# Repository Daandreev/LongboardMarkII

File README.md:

# LongboardMarkII

Ground up, over-engineered electric longboard

*****August 8, 2017*****

I want something under my ass that has enough potential energy packed into its batteries to fire a pound of bacon into the Asteroid Belt. 
Since nothing on the market fits the bill; I am building it myself.

With a sufficient disrespect for my own time and money I am learning every EE, ME, CS, Manufacturing technique necessary to complete aforementioned longboard.

The project started in my freshman year of college, Winter 2015.

[MarkI](https://www.instructables.com/id/Electric-Longboard-Mark-I/) was completed in the spring of 2016. It featured a whopping 35mph top speed, a pair of lead-acid scooter batteries giving it a theoretical range of about 4 miles of range, and a jaguaresque construction - requiring field-repairs every 2 miles.

MarkII was started soon after. Initially I focused on learning the electrical engineering skills necessary to create the Motor Drivers, BMS, and Headlights. 
	The Motor Drivers were my introduction to H-bridges and after creating a design that could vaguely spin a BLDC motor I opted out for [Vedder's VESC](http://vedder.se/2015/01/vesc-open-source-esc/)
	The BMS vas envisioned as an adaptive system that could be daisy chained across as many batteries as necessary, however that became more of a PCB design and manufacturing learning experience after I learned more about how they are made industrially.
	The headlights were and still are massively successful. With 5 watts of pure photon emission created by a triple bank of German OSRAM diodes, they are blindingly bright in all Red, Green, Blue and White colors. The issue is that I cant run them on more than 10% brightness without facing serious heat management issues.
	
In parallel with the electronics, I created a few iterations of the deck. I constructed my own longboard-deck press by molding an initial foam model with cement. The initial few attempts at carbon fiber-foam composites failed, however on the 3rd iteration of the Baltic Birch - Carbon fiber Composite, I was able to produce a beautiful deck that stands at 48in tall and flexes less than an inch with 500lb on it.

I also learned how to use a few CAD packages, and CNC equipment to make the mounting hardware for the motors. Learning from the flimsy construction of the MarkI motor mounts I designed my own longboard trucks to accommodate the installation of a pair of 2250Watt motors. My designs were based on the Caliber II Longboard trucks.

As it stands, just about everything made in the past year needs to be reiterated.

My main focus now, is to involve more people. My friend Anton Zaytsev has been diligently helping me create a 1.5kW charger and another offered to do some of the software. However, I think this project can bring together a serious community interested in progressing high-tech DIY electrical vehicles.

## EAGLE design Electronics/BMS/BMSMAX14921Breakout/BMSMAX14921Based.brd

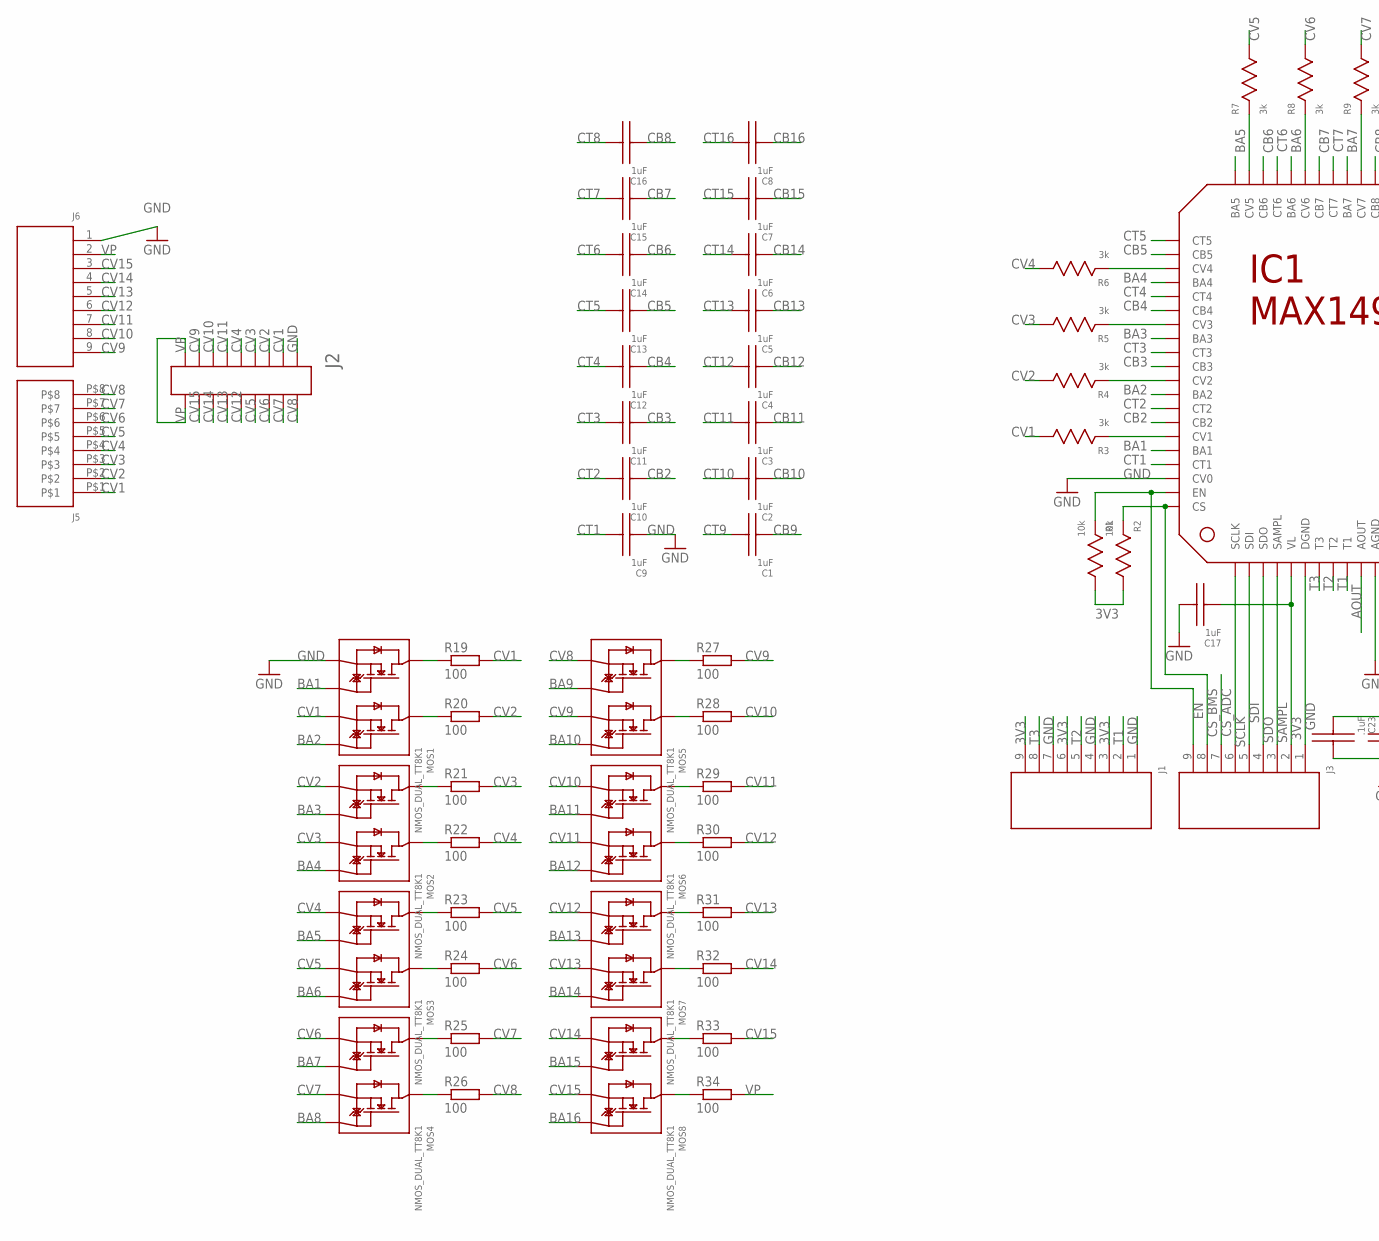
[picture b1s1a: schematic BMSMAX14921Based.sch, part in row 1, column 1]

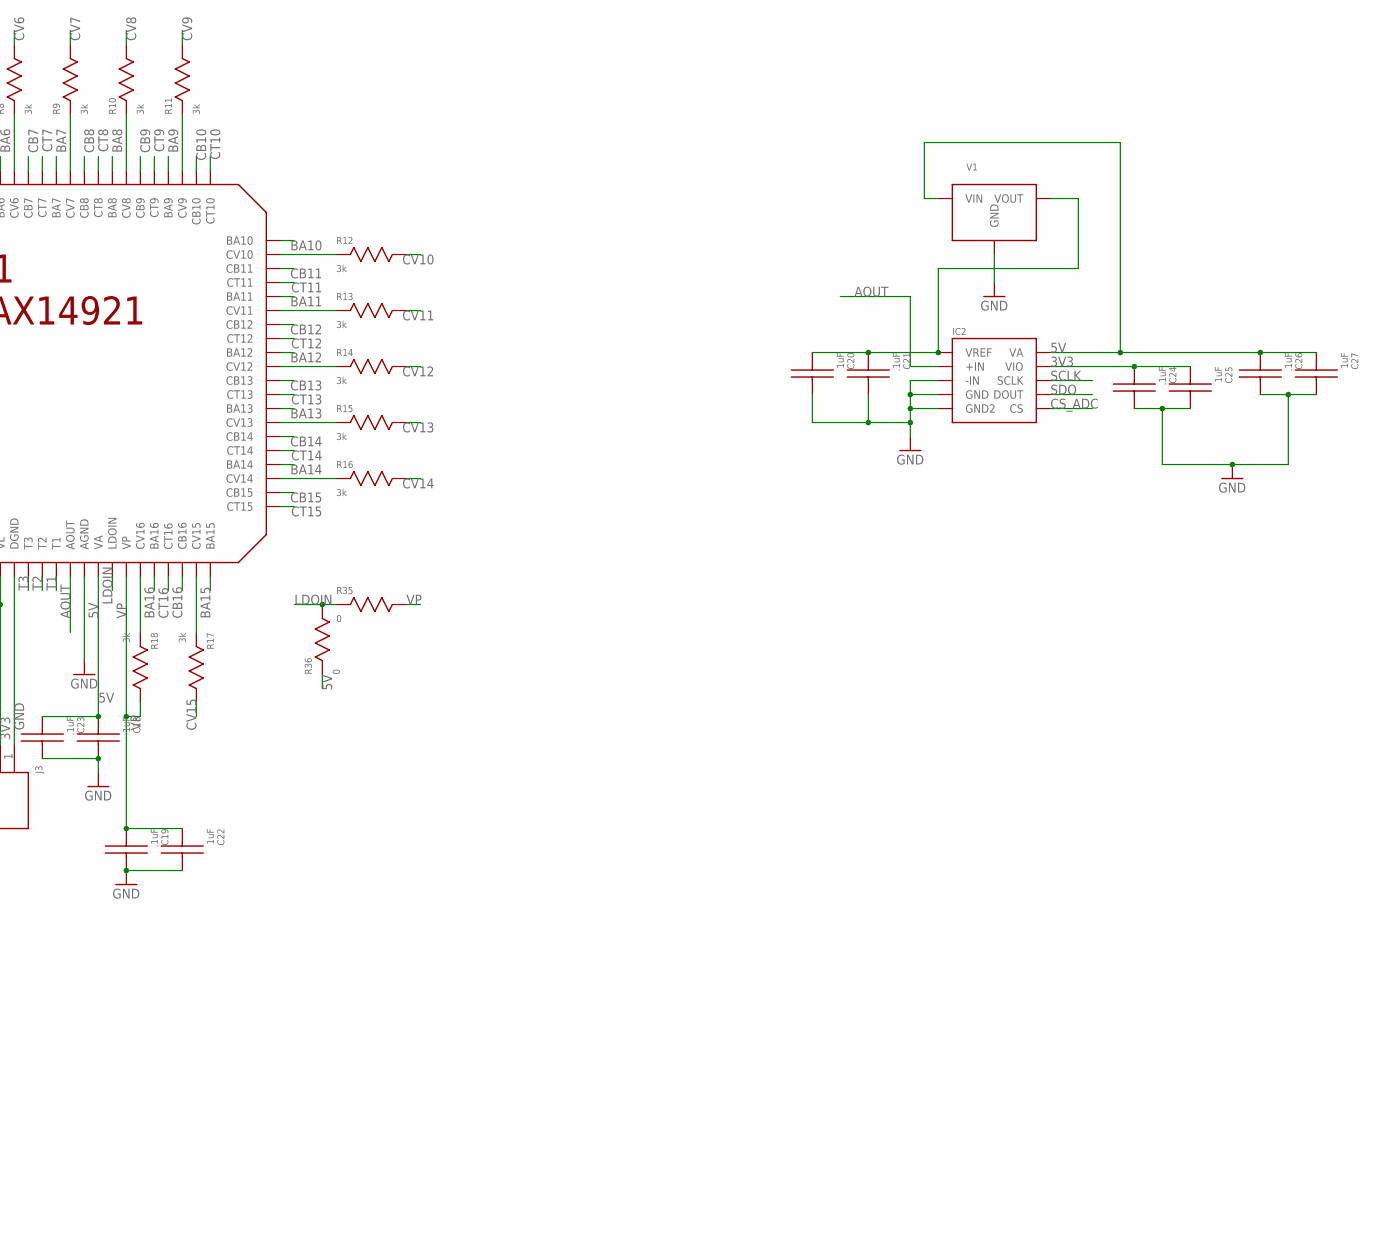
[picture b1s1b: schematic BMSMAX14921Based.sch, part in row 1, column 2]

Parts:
C1, C2, C3, C4, C5, C6, C7, C8, C9, C10, C11, C12, C13, C14, C15, C16, C17, C18, C20, C22, C25, C27: 1uF; 0805_(2012_METRIC)
C19, C21, C23, C24, C26: .1uF; 0805_(2012_METRIC)
IC1: MAX14921; 80TQFP
IC2: ADC141S626; 10-VSSOP
J1, J3, J6: CONNECTOR_9PIN; 9PIN_.1'
J2: CONNECTORJST2X9_2MM; CONNECTOR9X2_2MMPITCH
J5: CONNECTOR_8PIN; 8PIN_.1'
MOS1, MOS2, MOS3, MOS4, MOS5, MOS6, MOS7, MOS8: NMOS_DUAL_TT8K1; TSST8
R1, R2: 10k; 0805_(2012_METRIC)
R3, R4, R5, R6, R7, R8, R9, R10, R11, R12, R13, R14, R15, R16, R17, R18: 3k; 0805_(2012_METRIC)
R19, R20, R21, R22, R23, R24, R25, R26, R27, R28, R29, R30, R31, R32, R33, R34: 100; 0411V
R35, R36: 0; 0805_(2012_METRIC)
V1: REF3040; SOT-23

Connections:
3V3: C17.P$2, C24.P$2, C25.P$2, IC1.P$5 (VL), IC2.P$9 (VIO), J1.3, J1.6, J1.9, J3.2, R1.P$1, R2.P$1
5V: C18.P$2, C23.P$2, C26.P$2, C27.P$2, IC1.P$12 (VA), IC2.P$10 (VA), R36.P$2, V1.1 (VIN)
AOUT: IC1.P$10 (AOUT), IC2.P$2 (+IN)
BA1: IC1.P$76 (BA1), MOS1.P$2 (G1)
BA2: IC1.P$72 (BA2), MOS1.P$4 (G2)
BA3: IC1.P$68 (BA3), MOS2.P$2 (G1)
BA4: IC1.P$64 (BA4), MOS2.P$4 (G2)
BA5: IC1.P$60 (BA5), MOS3.P$2 (G1)
BA6: IC1.P$56 (BA6), MOS3.P$4 (G2)
BA7: IC1.P$52 (BA7), MOS4.P$2 (G1)
BA8: IC1.P$48 (BA8), MOS4.P$4 (G2)
BA9: IC1.P$44 (BA9), MOS5.P$2 (G1)
BA10: IC1.P$40 (BA10), MOS5.P$4 (G2)
BA11: IC1.P$36 (BA11), MOS6.P$2 (G1)
BA12: IC1.P$32 (BA12), MOS6.P$4 (G2)
BA13: IC1.P$28 (BA13), MOS7.P$2 (G1)
BA14: IC1.P$24 (BA14), MOS7.P$4 (G2)
BA15: IC1.P$20 (BA15), MOS8.P$2 (G1)
BA16: IC1.P$16 (BA16), MOS8.P$4 (G2)
CB2: C10.P$2, IC1.P$74 (CB2)
CB3: C11.P$2, IC1.P$70 (CB3)
CB4: C12.P$2, IC1.P$66 (CB4)
CB5: C13.P$2, IC1.P$62 (CB5)
CB6: C14.P$2, IC1.P$58 (CB6)
CB7: C15.P$2, IC1.P$54 (CB7)
CB8: C16.P$2, IC1.P$50 (CB8)
CB9: C1.P$2, IC1.P$46 (CB9)
CB10: C2.P$2, IC1.P$42 (CB10)
CB11: C3.P$2, IC1.P$38 (CB11)
CB12: C4.P$2, IC1.P$34 (CB12)
CB13: C5.P$2, IC1.P$30 (CB13)
CB14: C6.P$2, IC1.P$26 (CB14)
CB15: C7.P$2, IC1.P$22 (CB15)
CB16: C8.P$2, IC1.P$18 (CB16)
CS_ADC: IC2.P$6 (CS), J3.7
CS_BMS: IC1.P$80 (CS), J3.8, R2.P$2
CT1: C9.P$1, IC1.P$77 (CT1)
CT2: C10.P$1, IC1.P$73 (CT2)
CT3: C11.P$1, IC1.P$69 (CT3)
CT4: C12.P$1, IC1.P$65 (CT4)
CT5: C13.P$1, IC1.P$61 (CT5)
CT6: C14.P$1, IC1.P$57 (CT6)
CT7: C15.P$1, IC1.P$53 (CT7)
CT8: C16.P$1, IC1.P$49 (CT8)
CT9: C1.P$1, IC1.P$45 (CT9)
CT10: C2.P$1, IC1.P$41 (CT10)
CT11: C3.P$1, IC1.P$37 (CT11)
CT12: C4.P$1, IC1.P$33 (CT12)
CT13: C5.P$1, IC1.P$29 (CT13)
CT14: C6.P$1, IC1.P$25 (CT14)
CT15: C7.P$1, IC1.P$21 (CT15)
CT16: C8.P$1, IC1.P$17 (CT16)
CV1: J2.P$2, J5.P$1, MOS1.P$3 (S2), R3.P$1, R19.2
CV2: J2.P$3, J5.P$2, MOS2.P$1 (S1), R4.P$1, R20.2
CV3: J2.P$4, J5.P$3, MOS2.P$3 (S2), R5.P$1, R21.2
CV4: J2.P$5, J5.P$4, MOS3.P$1 (S1), R6.P$1, R22.2
CV5: J2.P$15, J5.P$5, MOS3.P$3 (S2), R7.P$1, R23.2
CV6: J2.P$16, J5.P$6, MOS4.P$1 (S1), R8.P$1, R24.2
CV7: J2.P$17, J5.P$7, MOS4.P$3 (S2), R9.P$1, R25.2
CV8: J2.P$18, J5.P$8, MOS5.P$1 (S1), R10.P$1, R26.2
CV9: J2.P$8, J6.9, MOS5.P$3 (S2), R11.P$1, R27.2
CV10: J2.P$7, J6.8, MOS6.P$1 (S1), R12.P$1, R28.2
CV11: J2.P$6, J6.7, MOS6.P$3 (S2), R13.P$1, R29.2
CV12: J2.P$14, J6.6, MOS7.P$1 (S1), R14.P$1, R30.2
CV13: J2.P$13, J6.5, MOS7.P$3 (S2), R15.P$1, R31.2
CV14: J2.P$12, J6.4, MOS8.P$1 (S1), R16.P$1, R32.2
CV15: J2.P$11, J6.3, MOS8.P$3 (S2), R17.P$1, R33.2
EN: IC1.P$79 (EN), J3.9, R1.P$2
GND: C9.P$2, C17.P$1, C18.P$1, C19.P$1, C20.P$1, C21.P$1, C22.P$1, C23.P$1, C24.P$1, C25.P$1, C26.P$1, C27.P$1, IC1.P$6 (DGND), IC1.P$11 (AGND), IC1.P$78 (CV0), IC2.P$3 (-IN), IC2.P$4 (GND), IC2.P$5 (GND2), J1.1, J1.4, J1.7, J2.P$1, J3.1, J6.1, MOS1.P$1 (S1), V1.3 (GND)
LDOIN: IC1.P$13 (LDOIN), R35.P$2, R36.P$1
unnamed: MOS1.P$7 (D1), MOS1.P$8 (D1), R19.1
unnamed: C20.P$2, C21.P$2, IC2.P$1 (VREF), V1.2 (VOUT)
unnamed: IC1.P$71 (CV2), R4.P$2
unnamed: IC1.P$67 (CV3), R5.P$2
unnamed: IC1.P$75 (CV1), R3.P$2
unnamed: IC1.P$63 (CV4), R6.P$2
unnamed: IC1.P$59 (CV5), R7.P$2
unnamed: IC1.P$55 (CV6), R8.P$2
unnamed: IC1.P$51 (CV7), R9.P$2
unnamed: IC1.P$47 (CV8), R10.P$2
unnamed: IC1.P$43 (CV9), R11.P$2
unnamed: IC1.P$39 (CV10), R12.P$2
unnamed: IC1.P$35 (CV11), R13.P$2
unnamed: IC1.P$31 (CV12), R14.P$2
unnamed: IC1.P$27 (CV13), R15.P$2
unnamed: IC1.P$23 (CV14), R16.P$2
unnamed: IC1.P$19 (CV15), R17.P$2
unnamed: IC1.P$15 (CV16), R18.P$2
unnamed: MOS1.P$5 (D2), MOS1.P$6 (D2), R20.1
unnamed: MOS2.P$7 (D1), MOS2.P$8 (D1), R21.1
unnamed: MOS2.P$5 (D2), MOS2.P$6 (D2), R22.1
unnamed: MOS3.P$7 (D1), MOS3.P$8 (D1), R23.1
unnamed: MOS3.P$5 (D2), MOS3.P$6 (D2), R24.1
unnamed: MOS4.P$7 (D1), MOS4.P$8 (D1), R25.1
unnamed: MOS4.P$5 (D2), MOS4.P$6 (D2), R26.1
unnamed: MOS5.P$7 (D1), MOS5.P$8 (D1), R27.1
unnamed: MOS5.P$5 (D2), MOS5.P$6 (D2), R28.1
unnamed: MOS6.P$7 (D1), MOS6.P$8 (D1), R29.1
unnamed: MOS6.P$5 (D2), MOS6.P$6 (D2), R30.1
unnamed: MOS7.P$7 (D1), MOS7.P$8 (D1), R31.1
unnamed: MOS7.P$5 (D2), MOS7.P$6 (D2), R32.1
unnamed: MOS8.P$7 (D1), MOS8.P$8 (D1), R33.1
unnamed: MOS8.P$5 (D2), MOS8.P$6 (D2), R34.1
SAMPL: IC1.P$4 (SAMPL), J3.3
SCLK: IC1.P$1 (SCLK), IC2.P$8 (SCLK), J3.6
SDI: IC1.P$2 (SDI), J3.5
SDO: IC1.P$3 (SDO), IC2.P$7 (DOUT), J3.4
T1: IC1.P$9 (T1), J1.2
T2: IC1.P$8 (T2), J1.5
T3: IC1.P$7 (T3), J1.8
VP: C19.P$2, C22.P$2, IC1.P$14 (VP), J2.P$9, J2.P$10, J6.2, R18.P$1, R34.2, R35.P$1

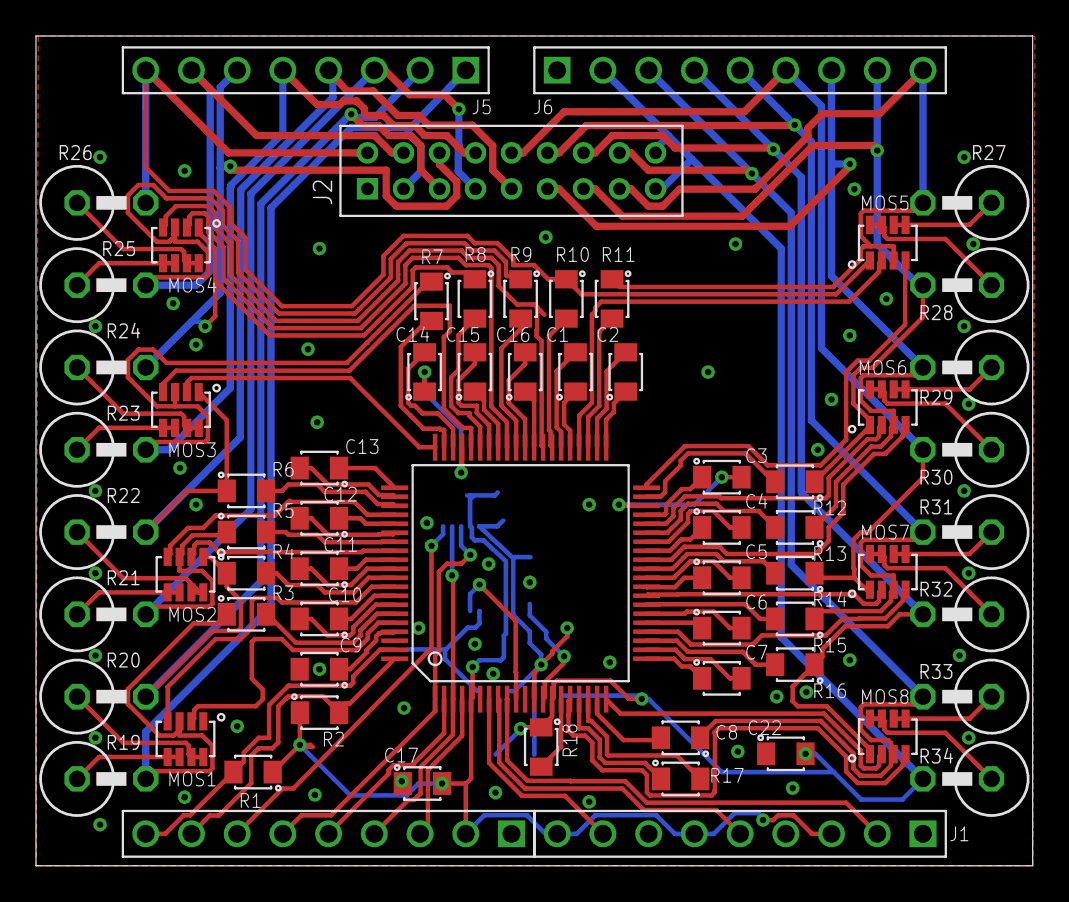
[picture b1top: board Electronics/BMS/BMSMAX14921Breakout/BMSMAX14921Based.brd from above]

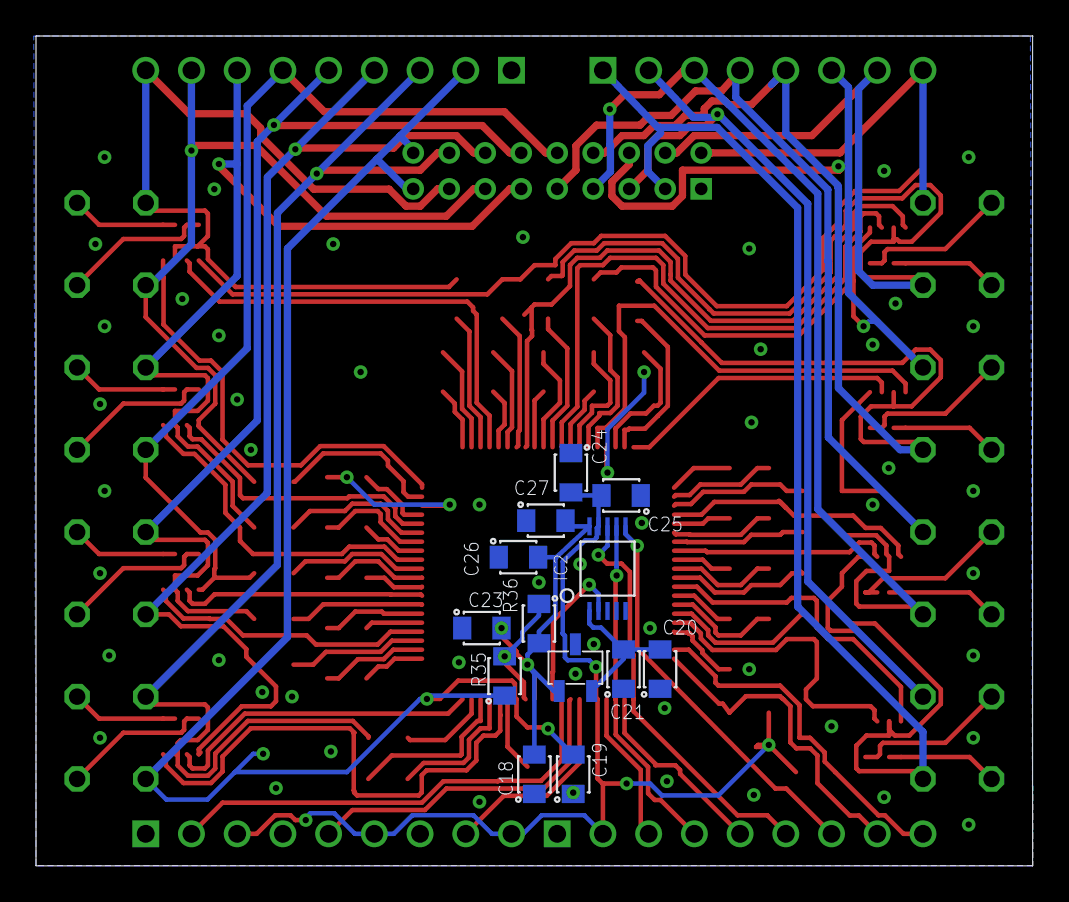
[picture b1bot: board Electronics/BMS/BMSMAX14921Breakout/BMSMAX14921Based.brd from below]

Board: 2 copper layers, 55.4 x 46.1 mm, 79 parts (13 on the bottom side), 111 nets.

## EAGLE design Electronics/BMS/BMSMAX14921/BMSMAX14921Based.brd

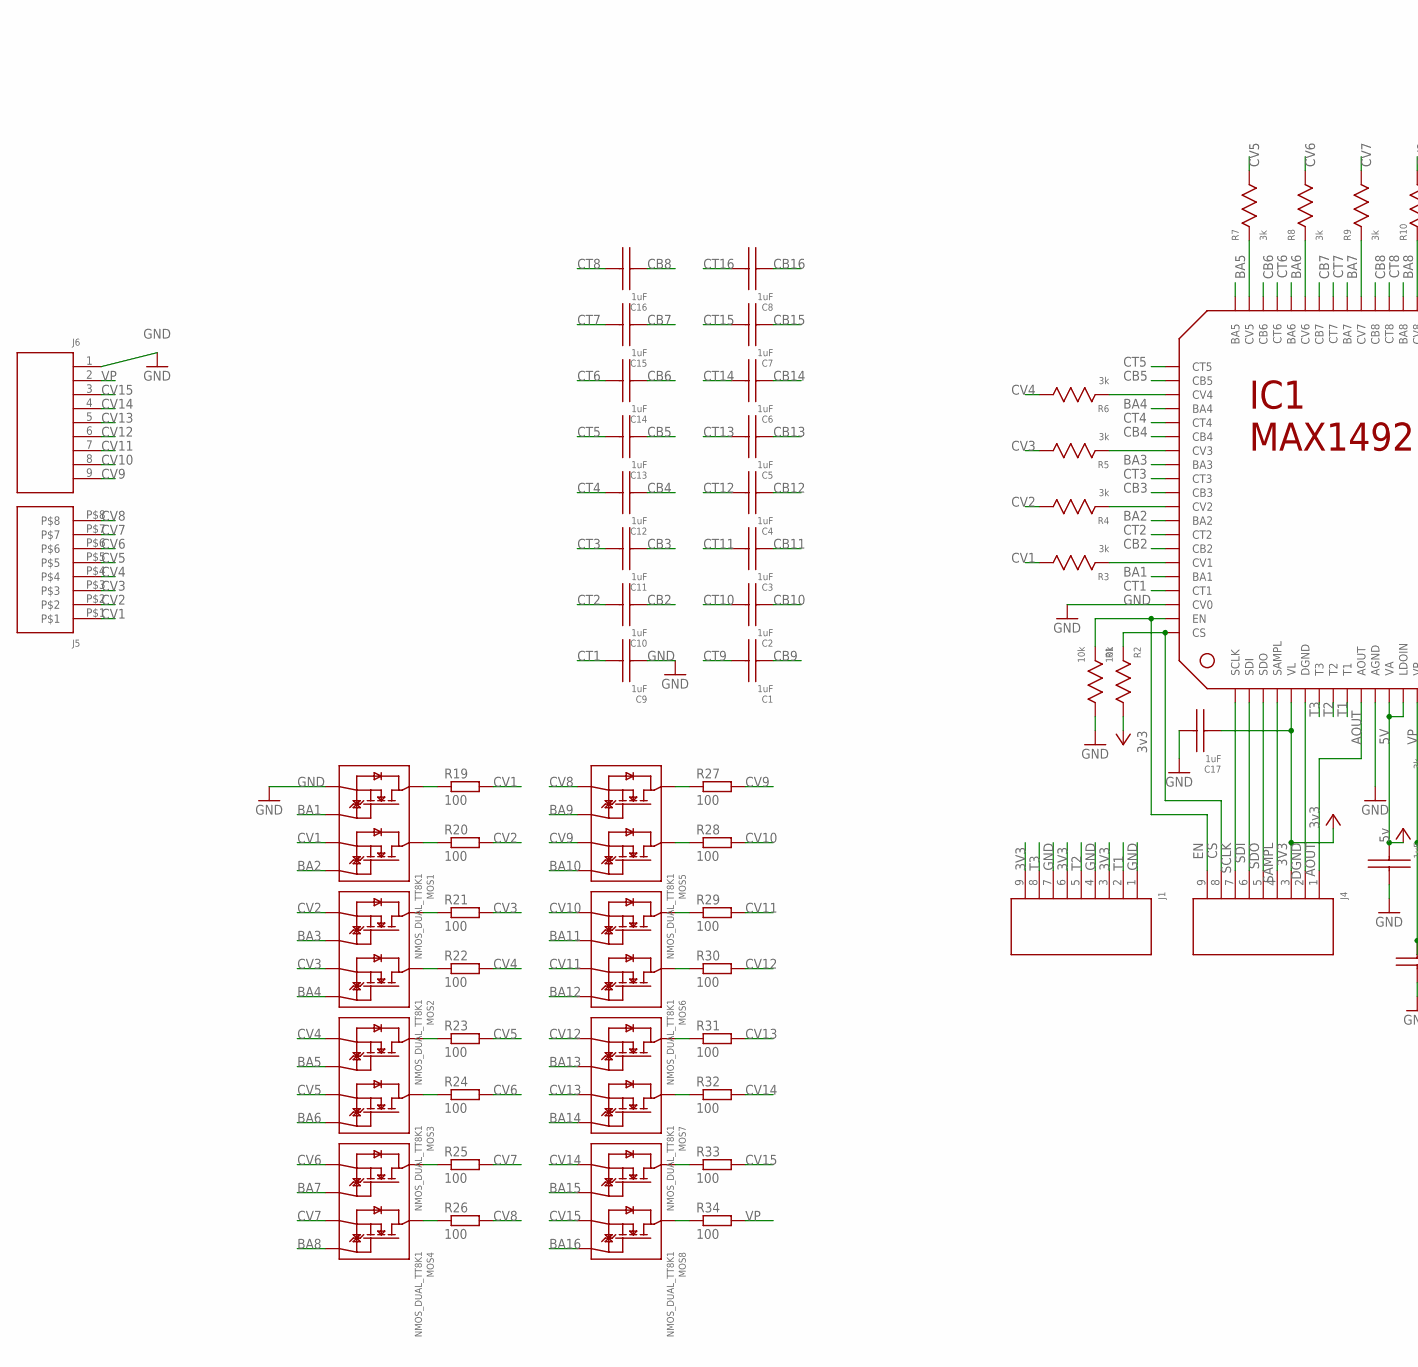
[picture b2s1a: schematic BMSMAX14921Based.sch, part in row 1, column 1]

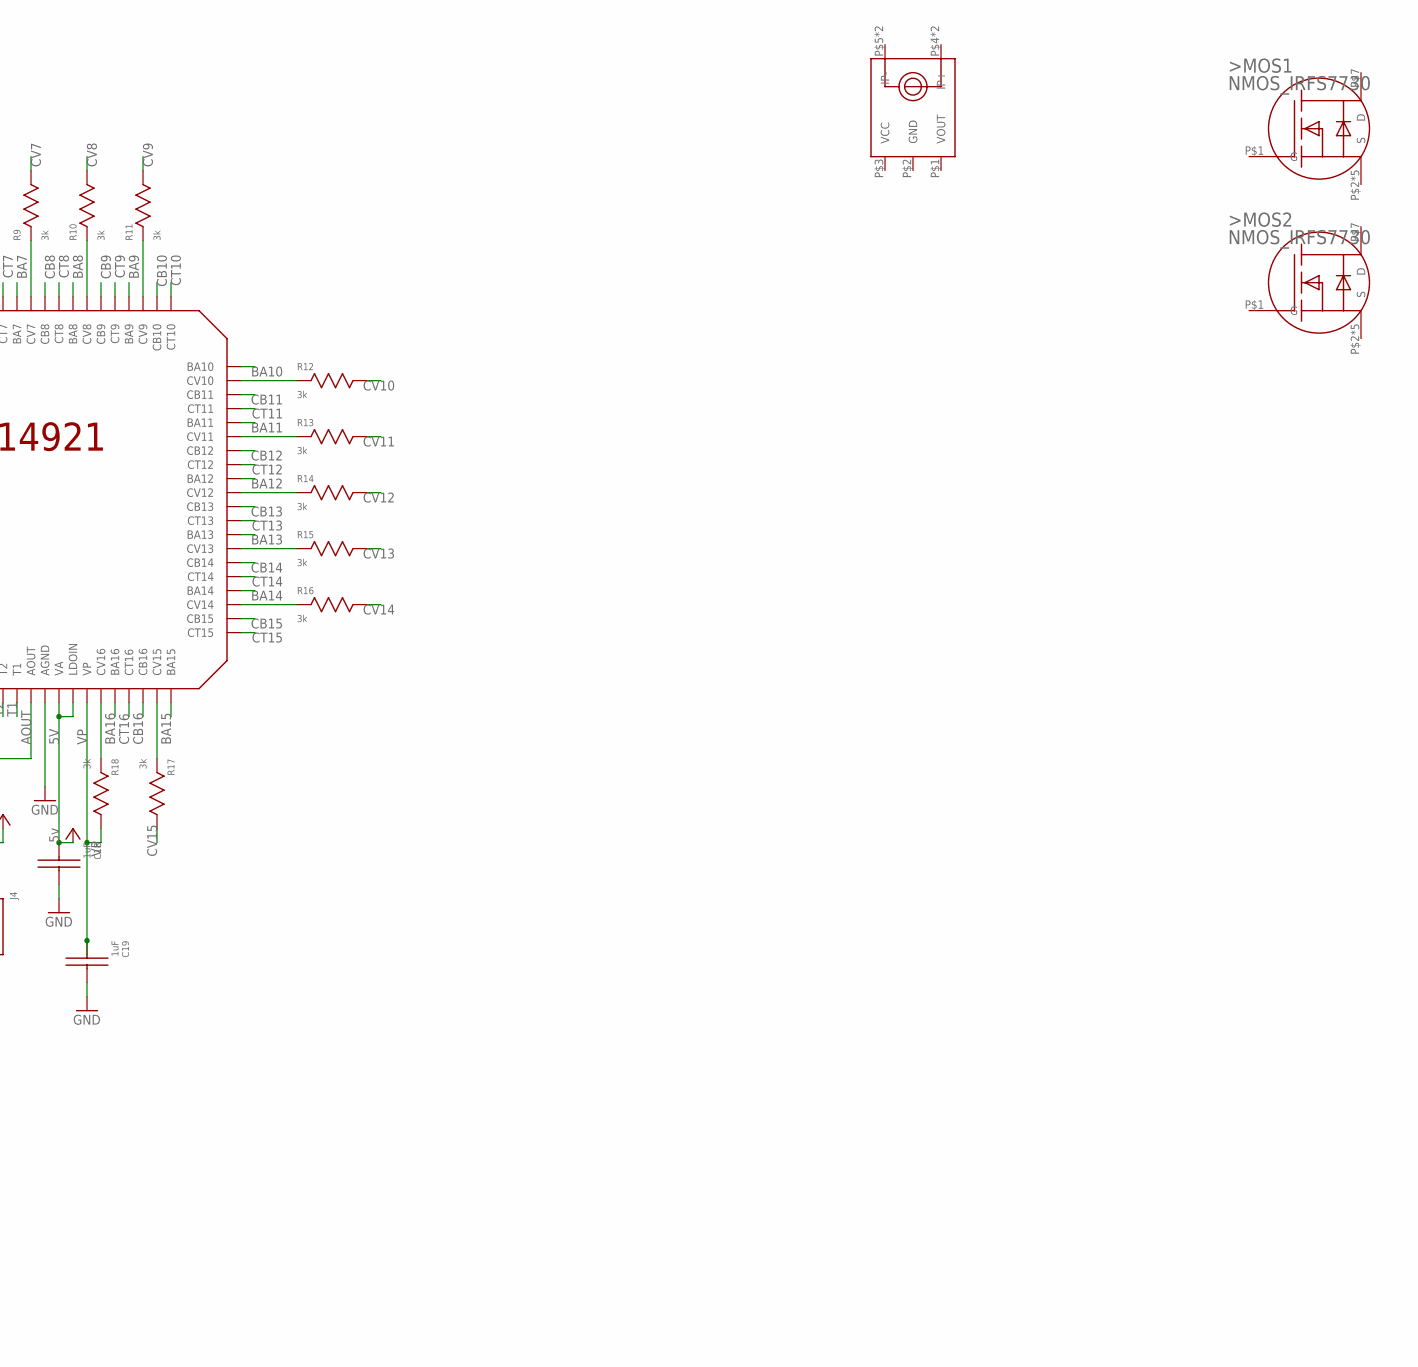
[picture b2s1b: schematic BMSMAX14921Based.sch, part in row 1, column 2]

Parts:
>MOS1, >MOS2: NMOS_IRFS7730; D2PAK-7PIN
C1, C2, C3, C4, C5, C6, C7, C8, C9, C10, C11, C12, C13, C14, C15, C16, C17, C18, C19: 1uF; 0805_(2012_METRIC)
IC1: MAX14921; 80TQFP
J1, J4, J6: CONNECTOR_9PIN; 9PIN_.1'
J5: CONNECTOR_8PIN; 8PIN_.1'
MOS1, MOS2, MOS3, MOS4, MOS5, MOS6, MOS7, MOS8: NMOS_DUAL_TT8K1; TSST8
R1, R2: 10k; 0805_(2012_METRIC)
R3, R4, R5, R6, R7, R8, R9, R10, R11, R12, R13, R14, R15, R16, R17, R18: 3k; 0805_(2012_METRIC)
R19, R20, R21, R22, R23, R24, R25, R26, R27, R28, R29, R30, R31, R32, R33, R34: 100; 0411V
U$1: ACS758XCB; CB5PFF

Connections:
3V3: C17.P$2, IC1.5 (VL), J1.3, J1.6, J1.9, J4.3, R2.P$1
5V: C18.P$2, IC1.12 (VA), IC1.13 (LDOIN)
AOUT: IC1.10 (AOUT), J4.1
BA1: IC1.76 (BA1), MOS1.P$2 (G1)
BA2: IC1.72 (BA2), MOS1.P$4 (G2)
BA3: IC1.68 (BA3), MOS2.P$2 (G1)
BA4: IC1.64 (BA4), MOS2.P$4 (G2)
BA5: IC1.60 (BA5), MOS3.P$2 (G1)
BA6: IC1.56 (BA6), MOS3.P$4 (G2)
BA7: IC1.52 (BA7), MOS4.P$2 (G1)
BA8: IC1.48 (BA8), MOS4.P$4 (G2)
BA9: IC1.44 (BA9), MOS5.P$2 (G1)
BA10: IC1.40 (BA10), MOS5.P$4 (G2)
BA11: IC1.36 (BA11), MOS6.P$2 (G1)
BA12: IC1.32 (BA12), MOS6.P$4 (G2)
BA13: IC1.28 (BA13), MOS7.P$2 (G1)
BA14: IC1.24 (BA14), MOS7.P$4 (G2)
BA15: IC1.20 (BA15), MOS8.P$2 (G1)
BA16: IC1.16 (BA16), MOS8.P$4 (G2)
CB2: C10.P$2, IC1.74 (CB2)
CB3: C11.P$2, IC1.70 (CB3)
CB4: C12.P$2, IC1.66 (CB4)
CB5: C13.P$2, IC1.62 (CB5)
CB6: C14.P$2, IC1.58 (CB6)
CB7: C15.P$2, IC1.54 (CB7)
CB8: C16.P$2, IC1.50 (CB8)
CB9: C1.P$2, IC1.46 (CB9)
CB10: C2.P$2, IC1.42 (CB10)
CB11: C3.P$2, IC1.38 (CB11)
CB12: C4.P$2, IC1.34 (CB12)
CB13: C5.P$2, IC1.30 (CB13)
CB14: C6.P$2, IC1.26 (CB14)
CB15: C7.P$2, IC1.22 (CB15)
CB16: C8.P$2, IC1.18 (CB16)
CS: IC1.80 (CS), J4.8, R2.P$2
CT1: C9.P$1, IC1.77 (CT1)
CT2: C10.P$1, IC1.73 (CT2)
CT3: C11.P$1, IC1.69 (CT3)
CT4: C12.P$1, IC1.65 (CT4)
CT5: C13.P$1, IC1.61 (CT5)
CT6: C14.P$1, IC1.57 (CT6)
CT7: C15.P$1, IC1.53 (CT7)
CT8: C16.P$1, IC1.49 (CT8)
CT9: C1.P$1, IC1.45 (CT9)
CT10: C2.P$1, IC1.41 (CT10)
CT11: C3.P$1, IC1.37 (CT11)
CT12: C4.P$1, IC1.33 (CT12)
CT13: C5.P$1, IC1.29 (CT13)
CT14: C6.P$1, IC1.25 (CT14)
CT15: C7.P$1, IC1.21 (CT15)
CT16: C8.P$1, IC1.17 (CT16)
CV1: J5.P$1, MOS1.P$3 (S2), R3.P$1, R19.2
CV2: J5.P$2, MOS2.P$1 (S1), R4.P$1, R20.2
CV3: J5.P$3, MOS2.P$3 (S2), R5.P$1, R21.2
CV4: J5.P$4, MOS3.P$1 (S1), R6.P$1, R22.2
CV5: J5.P$5, MOS3.P$3 (S2), R7.P$1, R23.2
CV6: J5.P$6, MOS4.P$1 (S1), R8.P$1, R24.2
CV7: J5.P$7, MOS4.P$3 (S2), R9.P$1, R25.2
CV8: J5.P$8, MOS5.P$1 (S1), R10.P$1, R26.2
CV9: J6.9, MOS5.P$3 (S2), R11.P$1, R27.2
CV10: J6.8, MOS6.P$1 (S1), R12.P$1, R28.2
CV11: J6.7, MOS6.P$3 (S2), R13.P$1, R29.2
CV12: J6.6, MOS7.P$1 (S1), R14.P$1, R30.2
CV13: J6.5, MOS7.P$3 (S2), R15.P$1, R31.2
CV14: J6.4, MOS8.P$1 (S1), R16.P$1, R32.2
CV15: J6.3, MOS8.P$3 (S2), R17.P$1, R33.2
DGND: IC1.6 (DGND), J4.2
EN: IC1.79 (EN), J4.9, R1.P$2
GND: C9.P$2, C17.P$1, C18.P$1, C19.P$1, IC1.11 (AGND), IC1.78 (CV0), J1.1, J1.4, J1.7, J6.1, MOS1.P$1 (S1), R1.P$1
unnamed: MOS1.P$7 (D1), MOS1.P$8 (D1), R19.1
unnamed: IC1.71 (CV2), R4.P$2
unnamed: IC1.67 (CV3), R5.P$2
unnamed: IC1.75 (CV1), R3.P$2
unnamed: IC1.63 (CV4), R6.P$2
unnamed: IC1.59 (CV5), R7.P$2
unnamed: IC1.55 (CV6), R8.P$2
unnamed: IC1.51 (CV7), R9.P$2
unnamed: IC1.47 (CV8), R10.P$2
unnamed: IC1.43 (CV9), R11.P$2
unnamed: IC1.39 (CV10), R12.P$2
unnamed: IC1.35 (CV11), R13.P$2
unnamed: IC1.31 (CV12), R14.P$2
unnamed: IC1.27 (CV13), R15.P$2
unnamed: IC1.23 (CV14), R16.P$2
unnamed: IC1.19 (CV15), R17.P$2
unnamed: IC1.15 (CV16), R18.P$2
unnamed: MOS1.P$5 (D2), MOS1.P$6 (D2), R20.1
unnamed: MOS2.P$7 (D1), MOS2.P$8 (D1), R21.1
unnamed: MOS2.P$5 (D2), MOS2.P$6 (D2), R22.1
unnamed: MOS3.P$7 (D1), MOS3.P$8 (D1), R23.1
unnamed: MOS3.P$5 (D2), MOS3.P$6 (D2), R24.1
unnamed: MOS4.P$7 (D1), MOS4.P$8 (D1), R25.1
unnamed: MOS4.P$5 (D2), MOS4.P$6 (D2), R26.1
unnamed: MOS5.P$7 (D1), MOS5.P$8 (D1), R27.1
unnamed: MOS5.P$5 (D2), MOS5.P$6 (D2), R28.1
unnamed: MOS6.P$7 (D1), MOS6.P$8 (D1), R29.1
unnamed: MOS6.P$5 (D2), MOS6.P$6 (D2), R30.1
unnamed: MOS7.P$7 (D1), MOS7.P$8 (D1), R31.1
unnamed: MOS7.P$5 (D2), MOS7.P$6 (D2), R32.1
unnamed: MOS8.P$7 (D1), MOS8.P$8 (D1), R33.1
unnamed: MOS8.P$5 (D2), MOS8.P$6 (D2), R34.1
SAMPL: IC1.4 (SAMPL), J4.4
SCLK: IC1.1 (SCLK), J4.7
SDI: IC1.2 (SDI), J4.6
SDO: IC1.3 (SDO), J4.5
T1: IC1.9 (T1), J1.2
T2: IC1.8 (T2), J1.5
T3: IC1.7 (T3), J1.8
VP: C19.P$2, IC1.14 (VP), J6.2, R18.P$1, R34.2

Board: 2 copper layers, 69 parts (0 on the bottom side), 109 nets, no tracks yet.

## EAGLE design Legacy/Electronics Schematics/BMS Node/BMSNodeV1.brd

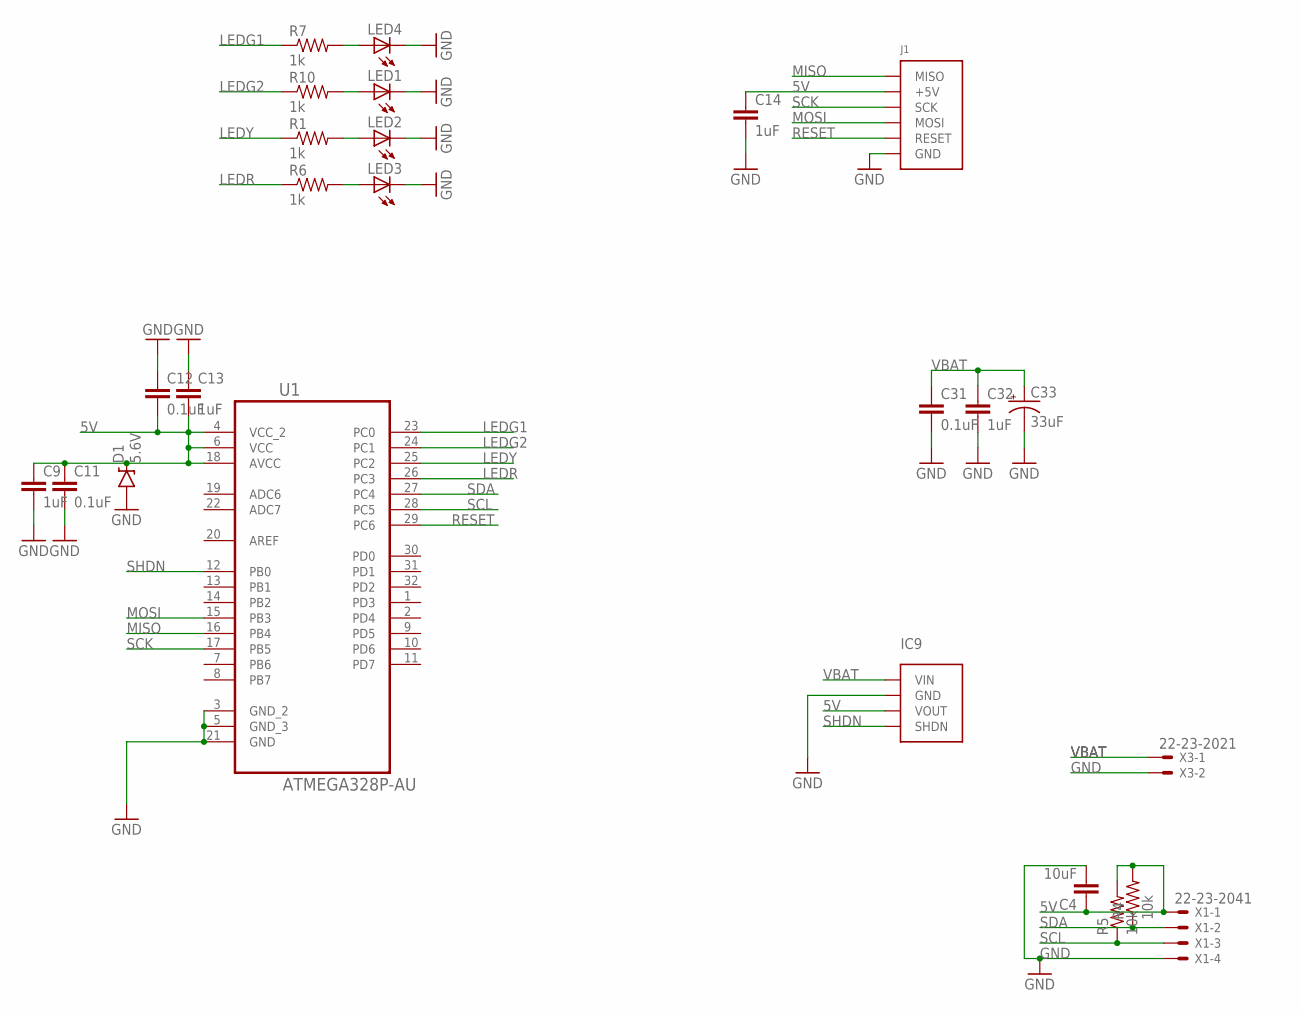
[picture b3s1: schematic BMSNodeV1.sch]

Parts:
C4: 10uF; 0805-CAP
C9, C13, C14, C32: 1uF; 0805-CAP
C11, C12, C31: 0.1uF; 0805-CAP
C33: 33uF; NIPPON_F80
D1: 5.6V; SOD-323
IC9: 5VBUCK_DANNY_CUSTOM_PCB; 4PIN_.1'
J1: ISPHEADER; 2X3PIN_.1'
LED1, LED2, LED3, LED4: LEDCHIPLED_0805; CHIPLED_0805
R1, R6, R7, R10: 1k; 0805
R4, R5: 10k; 0805
U1: ATMEGA328P-AU; QFP80P900X900X120-32N
X1: 22-23-2041
X3: 22-23-2021

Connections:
5V: C4.1, C9.1, C11.1, C12.2, C13.2, C14.1, D1.C, IC9.P$3 (VOUT), J1.P$2 (+5V), R4.2, R5.2, U1.4 (VCC_2), U1.6 (VCC), U1.18 (AVCC), X1.1
GND: C4.2, C9.2, C11.2, C12.1, C13.1, C14.2, C31.2, C32.2, C33.-, D1.A, IC9.P$2 (GND), J1.P$6 (GND), LED1.C, LED2.C, LED3.C, LED4.C, U1.3 (GND_2), U1.5 (GND_3), U1.21 (GND), X1.4, X3.2
LEDG1: R7.1, U1.23 (PC0)
LEDG2: R10.1, U1.24 (PC1)
LEDR: R6.1, U1.26 (PC3)
LEDY: R1.1, U1.25 (PC2)
MISO: J1.P$1 (MISO), U1.16 (PB4)
MOSI: J1.P$4 (MOSI), U1.15 (PB3)
unnamed: LED2.A, R1.2
unnamed: LED3.A, R6.2
unnamed: LED4.A, R7.2
unnamed: LED1.A, R10.2
RESET: J1.P$5 (RESET), U1.29 (PC6)
SCK: J1.P$3 (SCK), U1.17 (PB5)
SCL: R5.1, U1.28 (PC5), X1.3
SDA: R4.1, U1.27 (PC4), X1.2
SHDN: IC9.P$4 (SHDN), U1.12 (PB0)
VBAT: C31.1, C32.1, C33.+, IC9.P$1 (VIN), X3.1

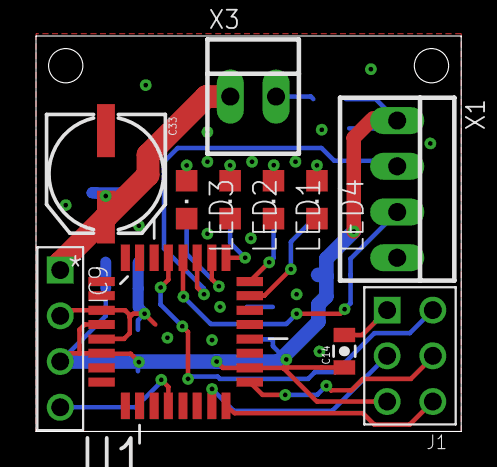
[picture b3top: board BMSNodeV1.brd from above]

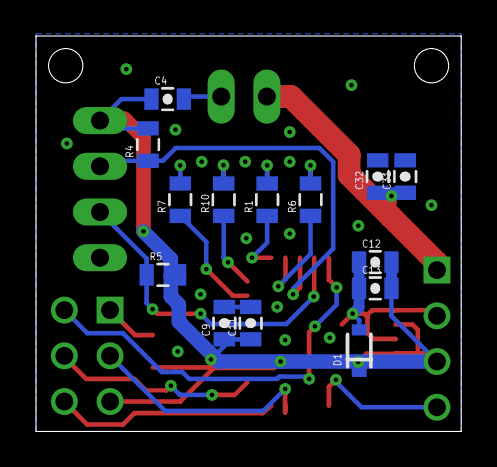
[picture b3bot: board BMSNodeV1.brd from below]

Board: 2 copper layers, 23.6 x 22.0 mm, 25 parts (14 on the bottom side), 18 nets.

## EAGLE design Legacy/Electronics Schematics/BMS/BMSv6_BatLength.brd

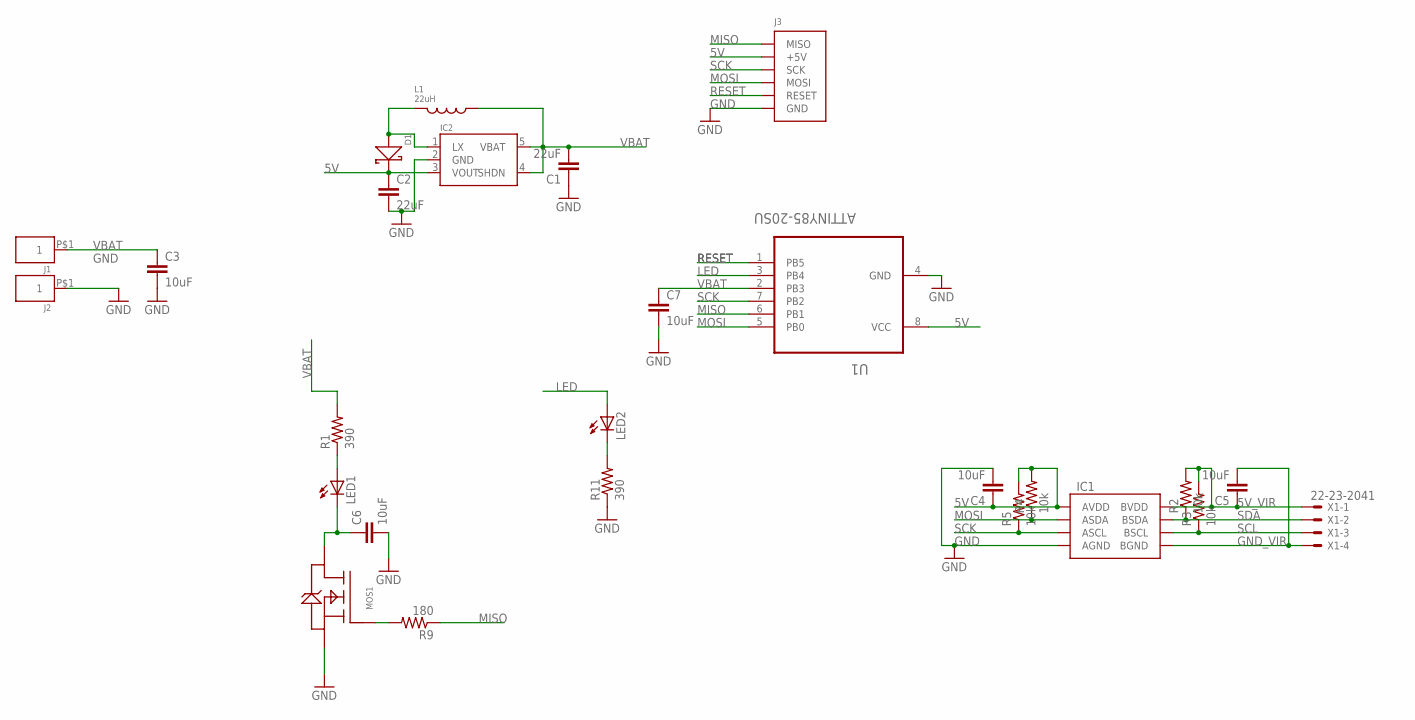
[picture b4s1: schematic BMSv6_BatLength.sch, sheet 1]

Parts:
C1, C2: 22uF; 0805-CAP
C3, C4, C5, C6, C7: 10uF; 0805-CAP
D1: DIODE_SCHOTTKYSOD-123; SOD-123
IC1: SI8600_DUALCHANNELISO; SOIC-8
IC2: SP6641; SOT-23
J1, J2: CONNECTOR_1PIN; SMD_PAD_.15X.25
J3: ISPHEADER; 2X3PIN_.1'
L1: 22uH; 6X6MM_IND
LED1, LED2: LEDCHIPLED_0805; CHIPLED_0805
MOS1: MOS_N_LOGIC_PSMN7R0; LFPAK
R1, R11: 390; 0805
R2, R3, R4, R5: 10k; 0805
R9: 180; 0805
U1: ATTINY85-20SU; SOIC127P798X216-8N
X1: 22-23-2041

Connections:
5V: C2.1, C4.1, D1.CATHODE, IC1.P$1 (AVDD), IC2.3 (VOUT), J3.P$2 (+5V), R4.2, R5.2, U1.8 (VCC)
5V_VIR: C5.1, IC1.P$8 (BVDD), R2.2, R3.2, X1.1
D: C6.1, LED1.C, MOS1.P$5 (DRAIN)
GND: C1.1, C2.2, C3.2, C4.2, C6.2, C7.2, IC1.P$4 (AGND), IC2.2 (GND), J2.P$1, J3.P$6 (GND), MOS1.P$1 (SOURCE), MOS1.P$2 (SOURCE), MOS1.P$3 (SOURCE), R11.1, U1.4 (GND)
GND_VIR: C5.2, IC1.P$5 (BGND), X1.4
LED: LED2.A, U1.3 (PB4)
MISO: J3.P$1 (MISO), R9.1, U1.6 (PB1)
MOSI: IC1.P$2 (ASDA), J3.P$4 (MOSI), R4.1, U1.5 (PB0)
unnamed: MOS1.P$4 (GATE), R9.2
unnamed: LED1.A, R1.1
unnamed: LED2.C, R11.2
unnamed: D1.ANODE, IC2.1 (LX), L1.P$1
RESET: J3.P$5 (RESET), U1.1 (PB5)
SCK: IC1.P$3 (ASCL), J3.P$3 (SCK), R5.1, U1.7 (PB2)
SCL: IC1.P$6 (BSCL), R3.1, X1.3
SDA: IC1.P$7 (BSDA), R2.1, X1.2
VBAT: C1.2, C3.1, C7.1, IC2.4 (SHDN), IC2.5 (VBAT), J1.P$1, L1.P$2, R1.2, U1.2 (PB3)

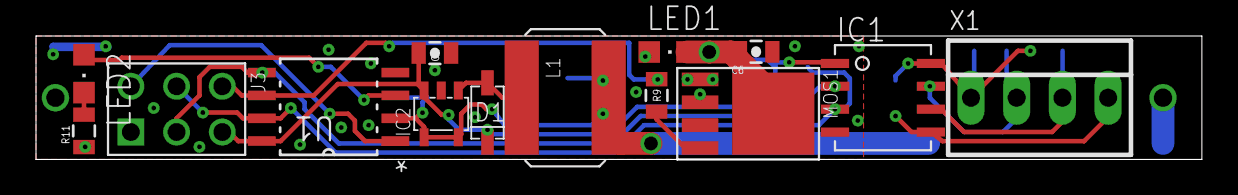
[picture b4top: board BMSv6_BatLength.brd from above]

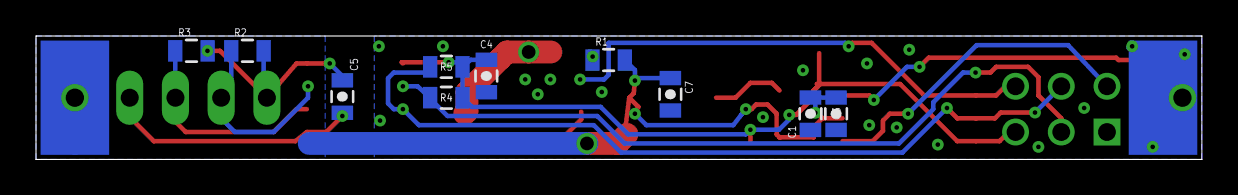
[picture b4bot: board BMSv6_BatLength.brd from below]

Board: 2 copper layers, 64.8 x 6.9 mm, 26 parts (12 on the bottom side), 17 nets.

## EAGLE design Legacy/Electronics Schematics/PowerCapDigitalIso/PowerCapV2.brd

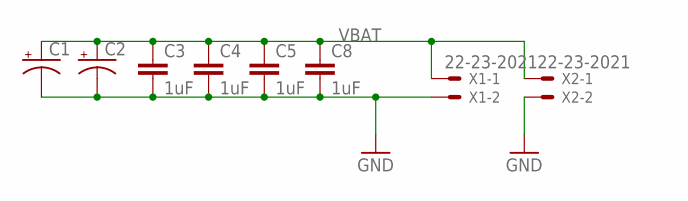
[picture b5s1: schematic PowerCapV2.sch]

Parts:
C1, C2: CAP_POLPTH4; CPOL-RADIAL-1000UF-25V
C3, C4, C5, C8: 1uF; 0805-CAP
X1, X2: 22-23-2021

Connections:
GND: C1.-, C2.-, C3.2, C4.2, C5.2, C8.2, X1.2, X2.2
VBAT: C1.+, C2.+, C3.1, C4.1, C5.1, C8.1, X1.1, X2.1

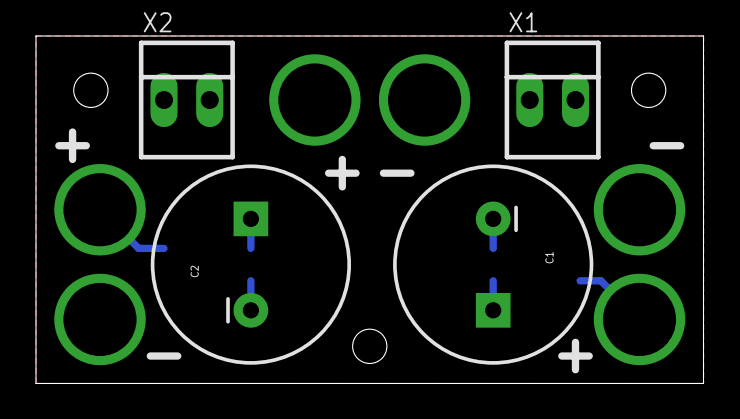
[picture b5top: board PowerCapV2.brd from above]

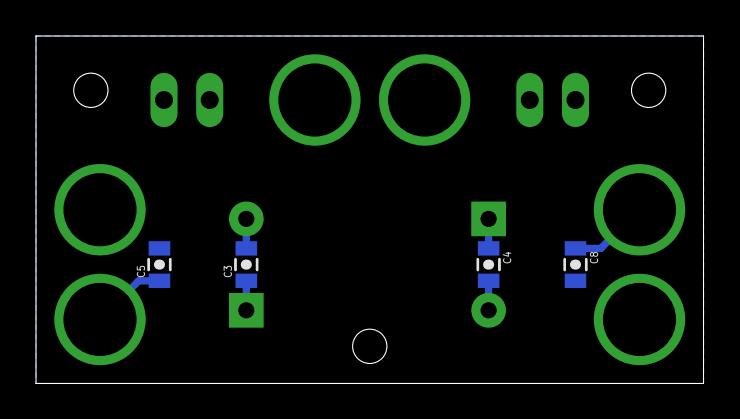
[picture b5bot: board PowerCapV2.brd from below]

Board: 2 copper layers, 37.1 x 19.3 mm, 8 parts (4 on the bottom side), 2 nets.

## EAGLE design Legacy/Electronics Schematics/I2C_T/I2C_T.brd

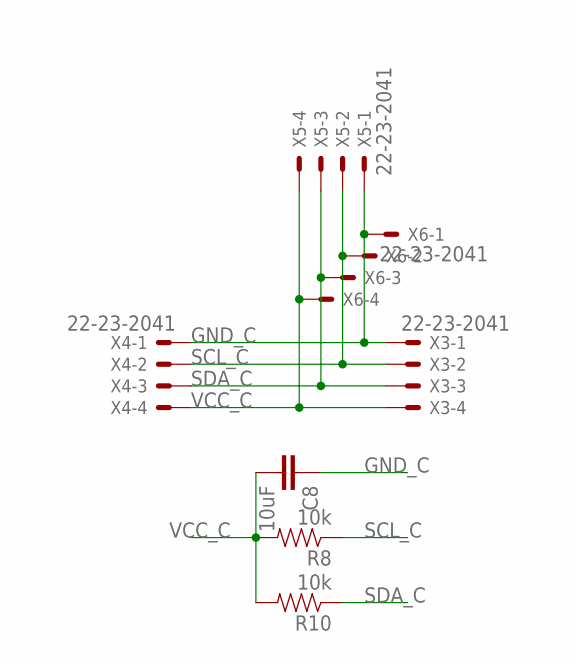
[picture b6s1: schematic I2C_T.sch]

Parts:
C8: 10uF; 0805-CAP
R8, R10: 10k; 0805
X3, X4, X5, X6: 22-23-2041

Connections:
GND_C: C8.1, X3.1, X4.1, X5.1, X6.1
SCL_C: R8.1, X3.2, X4.2, X5.2, X6.2
SDA_C: R10.1, X3.3, X4.3, X5.3, X6.3
VCC_C: C8.2, R8.2, R10.2, X3.4, X4.4, X5.4, X6.4

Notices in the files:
parts and their libraries:
SparkFun-Aesthetics: Licensing: Creative Commons ShareAlike 4.0 International - https://creativecommons.org/licenses/by-sa/4.0
